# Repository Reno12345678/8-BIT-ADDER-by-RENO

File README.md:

# 8-BIT-ADDER-by-RENO
Hello this is my 8-BIT ADDER project inspired by Hyperspace Pyrate
This project is a fully functional **8-bit adder** built using discrete components. It demonstrates the fundamental principles of binary addition using **2N3904 BJT transistors** as logic gates.

## Components Used

- **2N3904 BJT transistors**                                                                                                                                                         `152pcs`
- **220kΩ resistor for inputs**                                                                                                                                                      `184pcs`
- **47kΩ pull-up resistors**`50pcs`
- **LED**        `9pcs`                                                                                                                                              
- **PCB**          `8pcs`                  

## Overview

The adder is designed to take two 8-bit binary numbers as input and produce an 8-bit sum along with a carry-out bit. The circuit operates purely on discrete transistor logic without the use of integrated circuits.

## How It Works

Each bit of the adder is built using **transistor-based logic gates** that replicate standard digital addition circuits. The adder is composed of multiple **full-adders** connected in series to process each bit sequentially.

### Logic Implementation

- **Inputs**: A full-adder takes three inputs: two significant bits, `A` and `B`, and a carry-in bit`Cin`, from the previous stage.
- **Sum Calculation**: The sum output, `S`, is calculated using the formula: `S = A ⊕ B ⊕ Cin`, where `⊕` denotes the XOR (exclusive OR) operation.
- **Carry-Out Calculation**: The carry-out output, `Cout`, is determined using the formula: `Cout = (A AND B) OR (Cin AND (A ⊕ B))`.
- **Logic Gates**: The full-adder circuit consists of two XOR gates, two AND gates, and one OR gate to implement the sum and carry-out calculations.
- **Purpose**: Full-adders are used to add binary numbers and are the fundamental building blocks of arithmetic logic units (ALUs) in computers and other digital systems.
- **Outputs**: I used LEDs to represent the output bits.

## PCB

- **PCB is made in** [KiCAD](https://www.kicad.org/) **and produced in** [JLC PCB](https://jlcpcb.com/)
- [PCB GERBER](https://drive.google.com/file/d/1TC0HHmTJvVchm60jO_TXwn7dzBnb9_OO/view?usp=sharing) 

## Youtoube video

**-** just doing

## Other

This project is inspirated by [Hyperspace Pyrate](https://youtu.be/X31B1pVow1o?si=5MChZk4HNTxjwTem)
And if you want something you can type me on "reno888" discord
This is my first time doing something like this so you can type me what should I do better next time

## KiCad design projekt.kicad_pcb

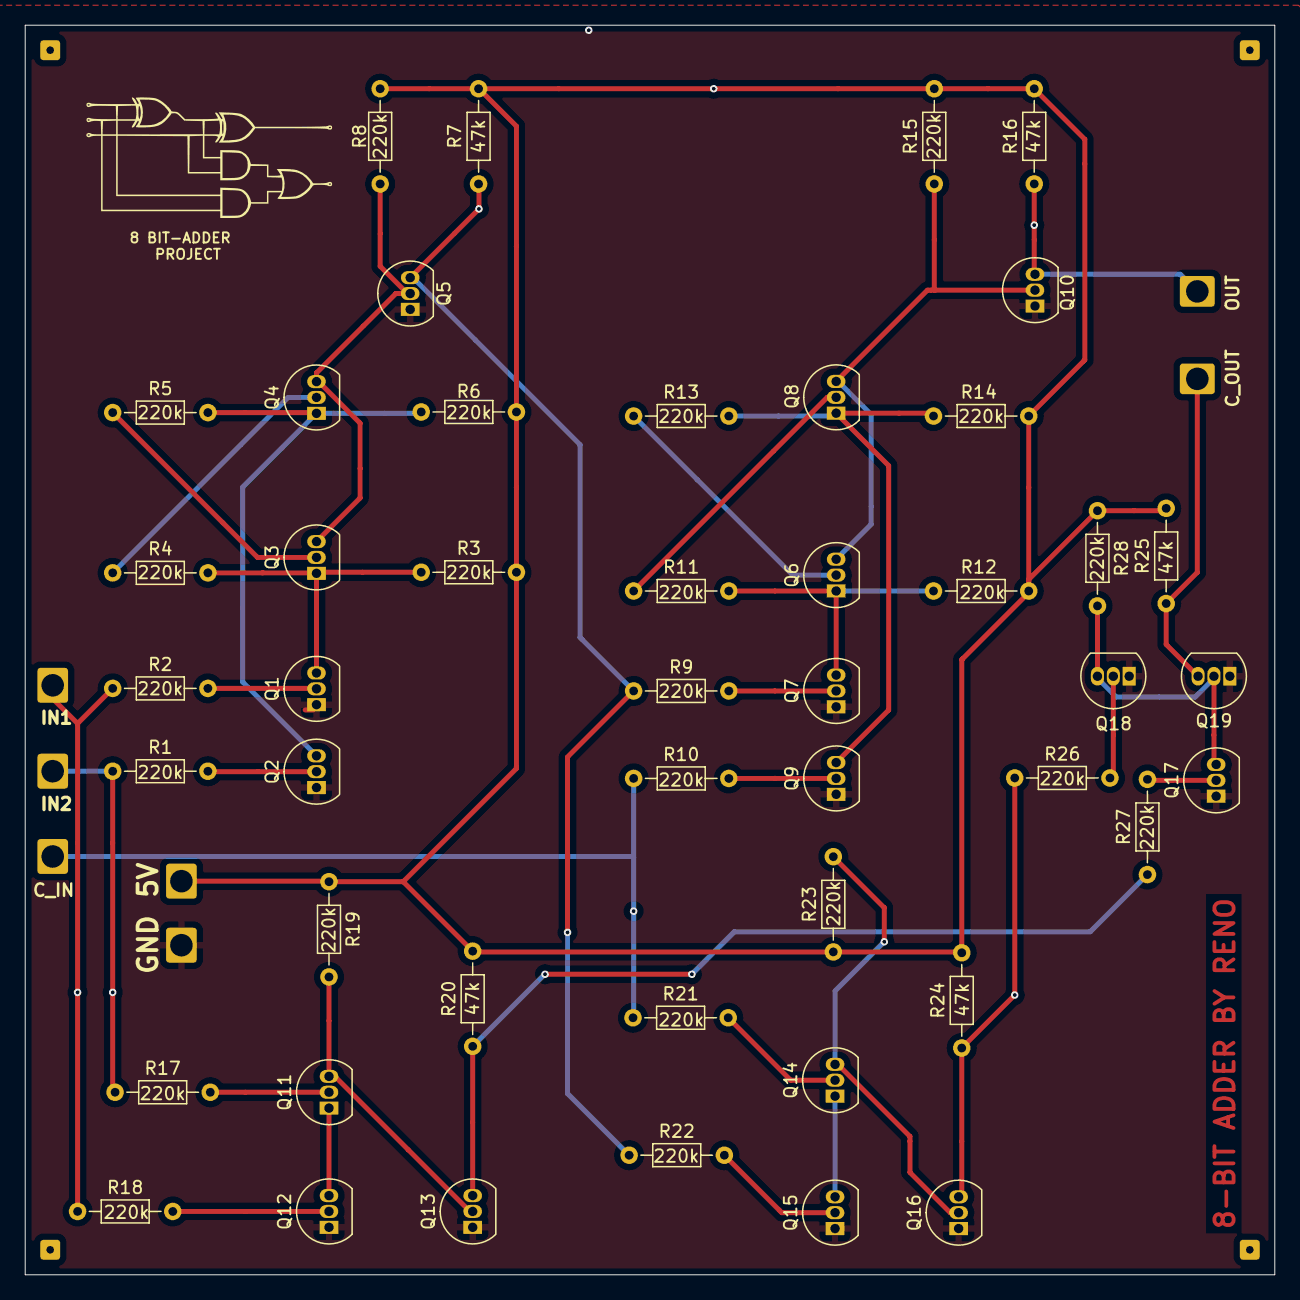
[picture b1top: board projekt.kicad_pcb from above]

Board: 4 copper layers, 100.0 x 100.0 mm, 54 parts (0 on the bottom side), 35 nets.

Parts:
J1, J2, J3, J4, J5, J6, J7: Conn_01x01_Pin; Hirose_DF63M-1P-3.96DSA_1x01_P3.96mm_Vertical
Q1, Q2, Q3, Q4, Q5, Q6, Q7, Q8, Q9, Q10, Q11, Q12, Q13, Q14, Q15, Q16, Q17, Q18, Q19: 2N3904; TO-92_Inline
R1, R2, R3, R4, R5, R6, R8, R9, R10, R11, R12, R13, R14, R15, R17, R18, R19, R21, R22, R23, R26, R27, R28: 220k; R_Axial_DIN0204_L3.6mm_D1.6mm_P7.62mm_Horizontal
R7, R16, R20, R24, R25: 47k; R_Axial_DIN0204_L3.6mm_D1.6mm_P7.62mm_Horizontal

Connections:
+5V: J3.1, R3.2, R6.2, R7.2, R8.2, R12.2, R14.2, R15.2, R16.2, R19.1, R20.2, R23.1, R24.2, R25.2, R28.1
GND: J5.1, Q1.1 (E), Q2.1 (E), Q5.1 (E), Q7.1 (E), Q9.1 (E), Q10.1 (E), Q12.1 (E), Q13.1 (E), Q15.1 (E), Q16.1 (E), Q17.1 (E), Q18.1 (E), Q19.1 (E)
unnamed: J1.1, R2.1, R18.1
unnamed: J2.1, R1.1, R17.1
unnamed: J4.1, Q10.3 (C), R16.1
unnamed: J6.1, R10.1, R21.1
unnamed: J7.1, Q19.3 (C), R25.1
unnamed: Q1.2 (B), R2.2
unnamed: Q1.3 (C), Q3.1 (E), R3.1, R4.2
unnamed: Q2.2 (B), R1.2
unnamed: Q2.3 (C), Q4.1 (E), R5.2, R6.1
unnamed: Q3.2 (B), R5.1
unnamed: Q3.3 (C), Q4.3 (C), Q5.2 (B), R8.1
unnamed: Q4.2 (B), R4.1
unnamed: Q5.3 (C), R7.1, R9.1, R22.1
unnamed: Q6.2 (B), R13.1
unnamed: Q6.1 (E), Q7.3 (C), R11.2, R12.1
unnamed: Q7.2 (B), R9.2
unnamed: Q8.2 (B), R11.1
unnamed: Q8.1 (E), Q9.3 (C), R13.2, R14.1
unnamed: Q9.2 (B), R10.2
unnamed: Q6.3 (C), Q8.3 (C), Q10.2 (B), R15.1
unnamed: Q11.2 (B), R17.2
unnamed: Q11.3 (C), Q13.2 (B), R19.2
unnamed: Q11.1 (E), Q12.3 (C)
unnamed: Q12.2 (B), R18.2
unnamed: Q13.3 (C), R20.1, R27.1
unnamed: Q14.2 (B), R21.2
unnamed: Q14.3 (C), Q16.2 (B), R23.2
unnamed: Q14.1 (E), Q15.3 (C)
unnamed: Q15.2 (B), R22.2
unnamed: Q16.3 (C), R24.1, R26.1
unnamed: Q17.2 (B), R27.2
unnamed: Q17.3 (C), Q18.3 (C), Q19.2 (B), R28.2
unnamed: Q18.2 (B), R26.2
